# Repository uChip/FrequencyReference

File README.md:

Programmable Frequency Reference   
================================  

This repository contains the design files and write-up for a Programmable Frequency Reference board based on the RALTRON RTX0230LC*.  The RTX0230LC is a ~1ppm accurate and stable crystal oscillator.  It is temperature compensated and tunable.  The oscillator drives the master clock of an ATmega328 microcontroller which then generates the output frequency by dividing down the master clock.  The ~2Vpp output signal is available on the BNC connector and has been impedance matched to 50 Ohms.

A set of common (and even**) frequencies from 10 MHz down to 152.6 Hz is selectable via a rotary encoder.  As each frequency is selected a representation of that frequency is shown on the display.  The following table shows the frequencies available and the displayed value.

NOTE that the display is NOT a measure of the produced frequency.

Within the microcontroller the TCXO clock drives Timer/Counter1.  The Timer/Counter1 is configured to count up until the value matches that in Output Compare Register A (OCR1A) at which point the counter is reset to zero and the output pin OC1A is toggled.  The values for OCR1A are selected from a table when the encoder knob is turned.

Alternatively, pressing the encoder knob will change the mode of the software and instead of choosing from a table, an integer divisor value (0 to 65535) is shown on the display and sent to OCR1A.  The count is incremented or decremented by turning the encoder knob.  The output frequency will be a function of the integer value as follows:

F_OUT = F_CPU / ( 2 * ( OCR1A + 1 ))

Pressing the encoder knob again returns the software to the common frequency mode.

The mode, table value and divisor can also be sent to the microcontroller over USB through the board's FTDI interface.  For details on USB programming, see the document USB_Programming.pdf in this repo.

The firmware folder contains an Arduino sketch and associated library that is source for the microcontroller code.

The next revision of the board will be designed to accomodate other oscillators should the RTX0230LC become unavailable or if even higher precision and stability are required.  Also, the firmware can be used on an "off the shelf" Arduino Uno to create a functional but less accurate frequency generator.  See the file VariationsOnATheme.pdf in this repo for more details.

NOTES  

\* The RALTRON RTX0230LC is a surplus part cheaply available (~$5.50 for 5 pieces at the time of this writing) on ebay. http://www.ebay.com/sch/i.html?_odkw=RTXO230&_osacat=0&_from=R40&_trksid=p2045573.m570.l1313.TR0.TRC0.H0.XRTX0230.TRS0&_nkw=RTX0230&_sacat=0

** Mostly.  All but the last are even numbered divisions of the master clock.  The last is the highest possible divisor, 65535, generating the lowest possible*** frequency.

*** Not really.  The firmware configures the timer/counter to be driven by the system clock.  By reconfiguring, the timer/counter could instead be driven by a prescaled clock.  Prescaler values are 1, 8, 64, 256, 1024, allowing for much lower frequency generation if needed.  The prescaler value can be set via the USB interface.

## Order PCBs  

If there is sufficient interest I will build and calibrate a batch of these to sell.  If you would like one, please contact me.

You can order this PCB directly from OSH Park.  Click on the following link.  
  * Programmable Frequency Reference - https://oshpark.com/shared_projects/a4BIq3K5 

See the Bill of Materials (BOM) file for a parts list.  

## Status  
  * Rev A PCB and firmware have been tested to be functional. Rev A is an earlier branch in this repo.  The design has since moved on to add support for other oscillators.
  * Rev B Not yet complete or tested.

## File Formats  

Hardware design files are in "CadSoft EAGLE PCB Design Software" .brd and .sch formats.  A free version of the software can be downloaded from www.cadsoftusa.com. 

The example code is in Arduino .ino format (text).  A free version of the Arduino software can be downloaded from www.arduino.cc. 

Documentation is generally done in Wordpad .rtf and Excel .xlsx.

Viewable versions of layout, schematic and documentation are generally available in common formats such as .pdf, .png, .jpg, .txt, etc.   

## Attributions

While the board layout, circuit design and microcontroller firmware are all my own, the idea for this project grew out of the 3 Dollar Precision Frequency Standard thread started by paulie on EEVBlog forum  http://www.eevblog.com/forum/projects/3-dollar-precision-frequency-standard/  

## Distribution License  

License:
<br /><span xmlns:dct="http://purl.org/dc/terms/" property="dct:title">Programmable Frequency Reference</span> by <a xmlns:cc="http://creativecommons.org/ns#" href="https://github.com/uChip/FrequencyReference" property="cc:attributionName" rel="cc:attributionURL">C.Schnarel</a> is licensed under a <a rel="license" href="http://creativecommons.org/licenses/by-sa/4.0/">Creative Commons Attribution-ShareAlike 4.0 International License</a>.

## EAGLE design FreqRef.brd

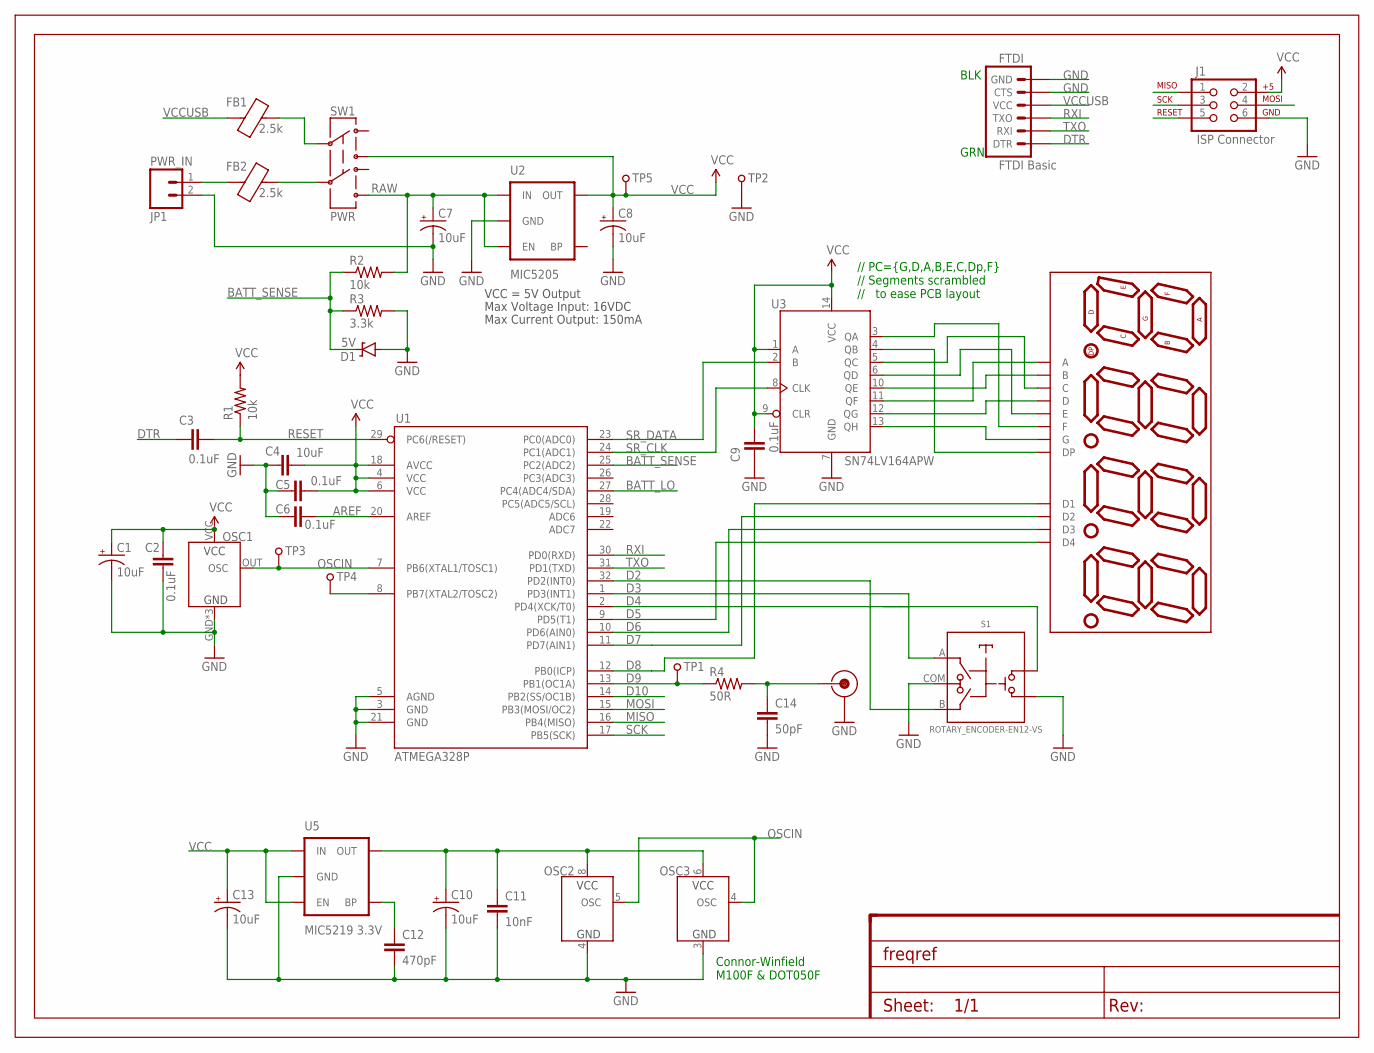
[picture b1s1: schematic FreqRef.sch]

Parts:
C1, C7, C8, C10, C13: 10uF; 0805-POL
C2, C3, C5, C6, C9: 0.1uF; 0805
C4: 10uF; 0805
C11: 10nF; 0805
C12: 470pF; 0805
C14: 50pF; 0805
D1: 5V; SOD-323
DISP1: HP_DISPLAY; DIL12
FB1, FB2: 2.5k; 0805
FRAME1: FRAME_LTR_CU_MARK; FR-LTR-ON-PCB
FTDI: FTDI Basic; 1X06
J1: ISP Connector; 2X3
J2: BNC_RIGHT-ANGLE; BNC-RIGHT-ANGLE
JP1: PWR_IN; MOLEX-1X2
OSC1: TCXORALTRON; TCXO
OSC2: TCXOM100; TCXO-3.2X5
OSC3: TCXODOT; TCXO-9X14
R1, R2: 10k; 0805
R3: 3.3k; 0805
R4: 50R; 0805
S1: ROTARY_ENCODER-EN12-VS; EN12-VS
SW1: PWR; 8X10_BUTTON_ROUND
TP1, TP2, TP3, TP4, TP5: TEST_POINT; BBD-VIA
U1: ATMEGA328P; TQFP32-08
U2: MIC5205; SOT23-5
U3: SN74LV164APW; TSSOP-14(TI)
U5: MIC5219 3.3V; SOT23-5

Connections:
AREF: C6.2, U1.20 (AREF)
BATT_LO: U1.27 (PC4(ADC4/SDA))
BATT_SENSE: D1.C, R2.1, R3.1, U1.25 (PC2(ADC2))
D2: S1.B, U1.32 (PD2(INT0))
D3: S1.A, U1.1 (PD3(INT1))
D4: S1.D, U1.2 (PD4(XCK/T0))
D5: DISP1.6 (D4), U1.9 (PD5(T1))
D6: DISP1.4 (D3), U1.10 (PD6(AIN0))
D7: DISP1.10 (D2), U1.11 (PD7(AIN1))
D8: DISP1.1 (D1), U1.12 (PB0(ICP))
D9: R4.1, TP1.P$1, U1.13 (PB1(OC1A))
D10: U1.14 (PB2(SS/OC1B))
DTR: C3.1, FTDI.1 (DTR)
GND: C1.2 (-), C2.1, C4.1, C5.1, C6.1, C7.2 (-), C8.2 (-), C9.1, C10.2 (-), C11.2, C12.2, C13.2 (-), C14.2, D1.A, FTDI.5 (CTS), FTDI.6 (GND), J1.6, J2.SHD, JP1.2, OSC1.GND, OSC1.SHLD1 (GND), OSC1.SHLD2 (GND), OSC2.4 (GND), OSC3.3 (GND), R3.2, S1.COM, S1.E, TP2.P$1, U1.3 (GND), U1.5 (AGND), U1.21 (GND), U2.2 (GND), U3.7 (GND), U5.2 (GND)
MISO: J1.1, U1.16 (PB4(MISO))
MOSI: J1.4, U1.15 (PB3(MOSI/OC2))
unnamed: DISP1.12 (A), U3.11 (QF)
unnamed: DISP1.11 (B), U3.10 (QE)
unnamed: DISP1.3 (C), U3.5 (QC)
unnamed: DISP1.8 (D), U3.12 (QG)
unnamed: TP4.P$1, U1.8 (PB7(XTAL2/TOSC2))
unnamed: DISP1.9 (F), U3.3 (QA)
unnamed: DISP1.7 (G), U3.13 (QH)
unnamed: DISP1.5 (DP), U3.4 (QB)
unnamed: C14.1, J2.CTR, R4.2
unnamed: DISP1.2 (E), U3.6 (QD)
unnamed: FB2.1, JP1.1
unnamed: C10.1 (+), C11.1, OSC2.8 (VCC), OSC3.6 (VCC), U5.5 (OUT)
unnamed: C12.1, U5.4 (BP)
unnamed: FB1.2, SW1.1C
OSCIN: OSC1.OUT (OSC), OSC2.5 (OSC), OSC3.4 (OSC), TP3.P$1, U1.7 (PB6(XTAL1/TOSC1))
RAW: C7.1 (+), R2.2, SW1.2NO, U2.1 (IN), U2.3 (EN)
RESET: C3.2, J1.5, R1.1, U1.29 (PC6(/RESET))
RXI: FTDI.3 (TXO), U1.30 (PD0(RXD))
SCK: J1.3, U1.17 (PB5(SCK))
SR_CLK: U1.24 (PC1(ADC1)), U3.8 (CLK)
SR_DATA: U1.23 (PC0(ADC0)), U3.2 (B)
TXO: FTDI.2 (RXI), U1.31 (PD1(TXD))
VCC: C1.1 (+), C2.2, C4.2, C5.2, C8.1 (+), C9.2, C13.1 (+), J1.2, OSC1.VCC, R1.2, SW1.1NO, TP5.P$1, U1.4 (VCC), U1.6 (VCC), U1.18 (AVCC), U2.5 (OUT), U3.1 (A), U3.9 (CLR), U3.14 (VCC), U5.1 (IN), U5.3 (EN)
VCCUSB: FB1.1, FTDI.4 (VCC)
VIN: FB2.2, SW1.2C

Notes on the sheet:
Max Voltage Input: 16VDC
Max Current Output: 150mA
VCC = 5V Output
// PC={G,D,A,B,E,C,Dp,F} // Segments scrambled // to ease PCB layout
BLK
GRN
Connor-Winfield M100F & DOT050F

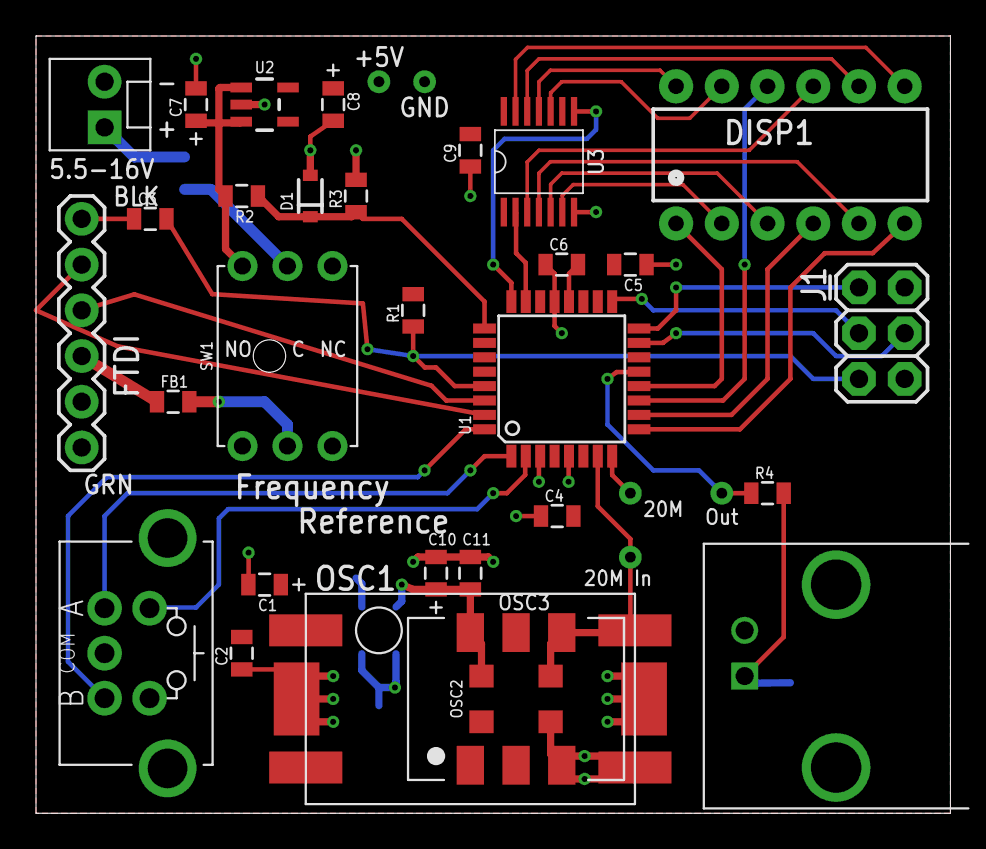
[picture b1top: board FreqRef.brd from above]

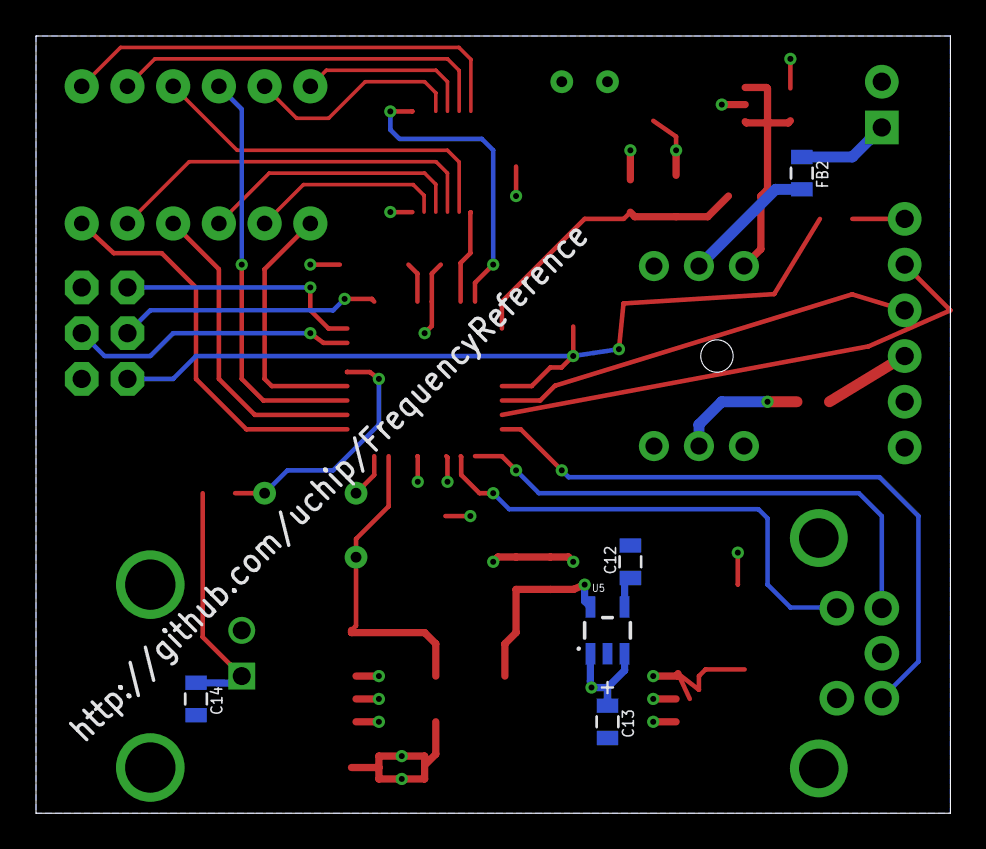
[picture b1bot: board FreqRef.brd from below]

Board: 2 copper layers, 50.8 x 43.2 mm, 41 parts (5 on the bottom side), 39 nets.

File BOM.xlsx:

Qty | Value | Device | Package | Parts | Source | Part # | Cost | Description
1 | 20.000000MHz | TCXO-RTXO230LC | TCXO | OSC1 | eBay |  | 1.0980000000000001 | Available here: http://www.ebay.com/itm/RALTRON-RTX0230LC-20-000MHz-TCXO-Oscill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
1 |  | PCB |  |  | OSHPark |  | 5.666666666666667
5 | 0.1uF | Capacitor | 0805 | C2, C3, C5, C6, C9 | Digi-Key | 399-1171-1-ND | 0.26650000000000001 | Capacitor
1 | 10k | Resistor | 0805 | R1 | Digi-Key | 311-10.0KLRCT-ND | 5.4000000000000003E-3 | Resistor
1 | 10uF | Capacitor | 0805 | C4 | Digi-Key | 587-2225-1-ND | 0.26 | Capacitor
3 | 10uF | Capacitor | 0805-POL | C1, C7, C8 | Digi-Key | 478-8456-1-ND | 1.4034
1 | 15k | Resistor | 0805 | R2 | Digi-Key | 311-15.0KCRCT-ND | 8.3999999999999995E-3 | Resistor
2 | 2.5k | FERRITE_BEAD | 0805 | FB1, FB2 | Digi-Key | 1276-6377-1-ND | 0.2 | Ferrite Bead, value is Resistance@Frequency (typ 100 MHz)
1 | 49.9R | Resistor | 0805 | R4 | Digi-Key | 311-49.9CRCT-ND | 0.1363 | Resistor
1 | 5V | Diode, zener, 4.7V | SOD-323 | D1 | Digi-Key | 568-6286-1-ND | 8.3999999999999995E-3 | Zener Diode
1 | 4.99k | Resistor | 0805 | R3 | Digi-Key | 311-4.99KCRCT-ND | 8.3999999999999995E-3 | Resistor
1 | ATMEGA328P | ATMEGA328P | TQFP32-08 | U1 | Digi-Key | ATMEGA328P-AURCT-ND | 3.7
1 | BNC_RIGHT-ANGLE | BNC connector | BNC-RIGHT-ANGLE | J2 | Digi-Key | A97553-ND | 2.0299999999999998 | TE Connectivity AMP Connectors 1-1337543-0, Digi-Key #A97553-ND
1 | FTDI Basic | pins | 1X06 | FTDI | SparkFun | PRT-00116 | 0.22499999999999998 | break-away pins straight or right angle (6-pins)
1 | HP_DISPLAY | HP_DISPLAY | DIL12 | DISP1 | SparkFun | COM-12710 | 2.95 | SparkFun COM-12710
1 | MIC5205 | Voltage Regulator, LDO | SOT23-5 | U2 | Digi-Key | 576-1262-1-ND | 0.62 | Voltage Regulator LDO
1 | PWR | SWITCH,BUTTON,ROUND,7MM | 8X10_BUTTON_ROUND | SW1 | Mouser | 611-PVB6THTEE300NS | 1.33 | BETA! SB0003 - Switch, DPDT, PTH, 200mA, 14V, 7mm ROUND CAP
1 | PWR_IN | Connector | MOLEX-1X2 | JP1 | SparkFun | PRT-08233 | 0.45 | Standard 2-pin 0.1 header. Use with"
1 | Switch | ROTARY_ENCODER | EN12-VS | S1 | Digi-Key | 987-1198-ND | 1.1100000000000001 | Rotary Encoder with push-button switch.
1 | SN74LV164APW | SN74LV164APW | TSSOP-14(TI) | U3 | Digi-Key | 296-3788-1-ND | 0.46 | 8-BIT SERIAL-IN PARALLEL-OUT SHIFT REGISTER with clear
 |  |  |  |  |  |  | 21.936466666666664

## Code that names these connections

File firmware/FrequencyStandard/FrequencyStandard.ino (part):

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#include <Timer1.h>

// Pins to drive Segment Shift Register
#define SR_DATA A0
#define SR_CLK A1

// Serial interface pins (defined in serial lib)
//#define RCV 0
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};

// Battery level measurement
#define BATT_SENSE A2

// Frequency Signal Out
#define F_OUT 9
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  Serial.println("Reference Frequency Generator");  // set up the segment control pins

  // set up sense pins
  pinMode(BATT_SENSE, INPUT);

  // set up the button input pin
  pinMode(BUTTON, INPUT_PULLUP);
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  if(button.read() == LOW) {mode = DIVISOR;} else {mode = TABLE_VALUES;}

  // set up the display SR control pins
  pinMode(SR_DATA, OUTPUT);
  pinMode(SR_CLK, OUTPUT);
  
  // set up the digit control pins
  pinMode(DIGIT_1, OUTPUT);
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// Do some flashy stuff to show display works and display battery level
//=====================================================================
void startLoop(){
  int16_t raw = 0;
  digitalWrite(REMOTE, HIGH);
  digitalWrite(CAL, HIGH);
  digitalWrite(BATT_LO, HIGH);
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
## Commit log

2015-09-01 :confetti_ball: Added .gitattributes & .gitignore files
2015-09-01 Initial Commit of schematic & board
    Complete design, but not necessarily final.
2015-09-03 Rev A board as ordered
    Minor changes for ordering. Added OSHPark renderings. Started writing
    firmware and GitHub cover.
2015-09-03 Start of Rev-B
    Change name to FrequencyReference.
    Added part num to BNC connector.
2015-09-03 README updates
    Noting that design is not ready for distribution.
2015-09-03 README edits
    fixed board render sizes
2015-09-03 README Edits
    Make table into a picture
2015-09-03 more README edits
2015-09-03 README edits
2015-09-03 More documentation work
2015-09-04 More documentation and comment revisions
2015-09-04 Application now compiles
2015-09-07 More docs. Rev-B layout. Debugged sketch.
    Continue documentation. Added two oscillator options to PCB schematic
    and layout. Debugged sketch on Redboard.
2015-09-16 Software debug. Schematic values. Added photos.
2015-09-16 More pictures & doc edits.
2015-09-16 Added library. Updated freq table.
2015-09-16 Syncing links. Updating BOM.
2015-09-16 Updating docs and creating PDFs.
2015-09-16 Added library attributions and release dates.
2015-09-16 PNG Format schematic and layout.
2015-09-17 Added docs for 20MHz support in IDE
2015-09-17 Docs updates
2015-09-20 Code formatting changes. A couple more OCXOs.
2015-09-27 Expanded firmware README
    Added Unbricking story
2015-10-12 Investigated a couple more XOs

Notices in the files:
parts and their libraries:
SparkFun-Connectors: Licensing: Creative Commons ShareAlike 4.0 International - https://creativecommons.org/licenses/by-sa/4.0
SparkFun-Capacitors: Licensing: CC v3.0 Share-Alike You are welcome to use this library for commercial purposes.
